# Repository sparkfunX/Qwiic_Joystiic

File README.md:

# Qwiic_Joystiic
Thumbstick Breakout for the Qwiic System
<br/><br/>
Factory Default I2C Slave Address: 0x20<br/>
<br/>
<h3 style="text-decoration: underline;">I2C Registers</h3><br/>
| Address | Contents |
| ------- | -------- |
| 0x00-0x01 | Horizontal Position (MSB First) |
| 0x02-0x03 | Vertical Position (MSB First) |
| 0x04 | Button Position |
| 0x06 | Current I2C Slave Address from EEPROM |
<br/>
<h3 style="text-decoration: underline;">I2C Commands</h3><br/>
| Address | Command |
| ------- | ------- |
| 0x05 | Set I2C Slave Address |

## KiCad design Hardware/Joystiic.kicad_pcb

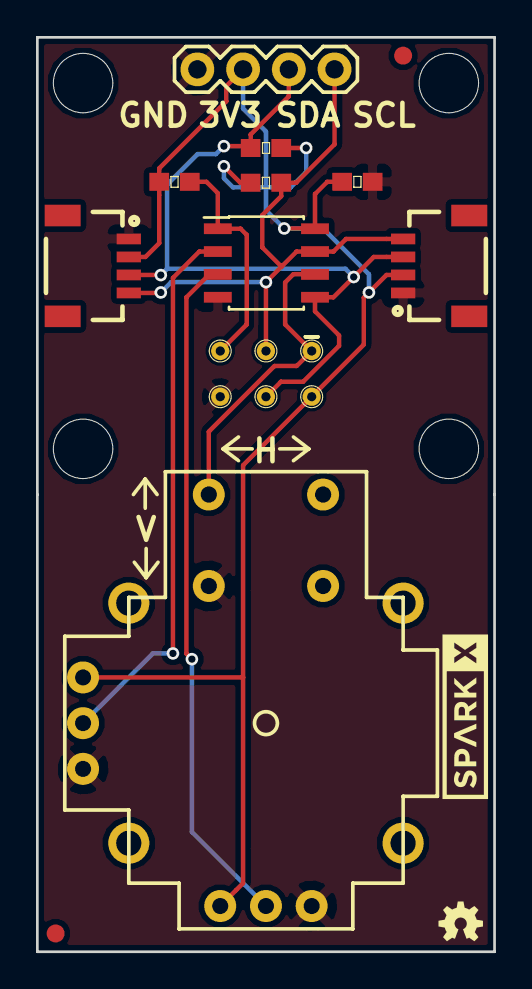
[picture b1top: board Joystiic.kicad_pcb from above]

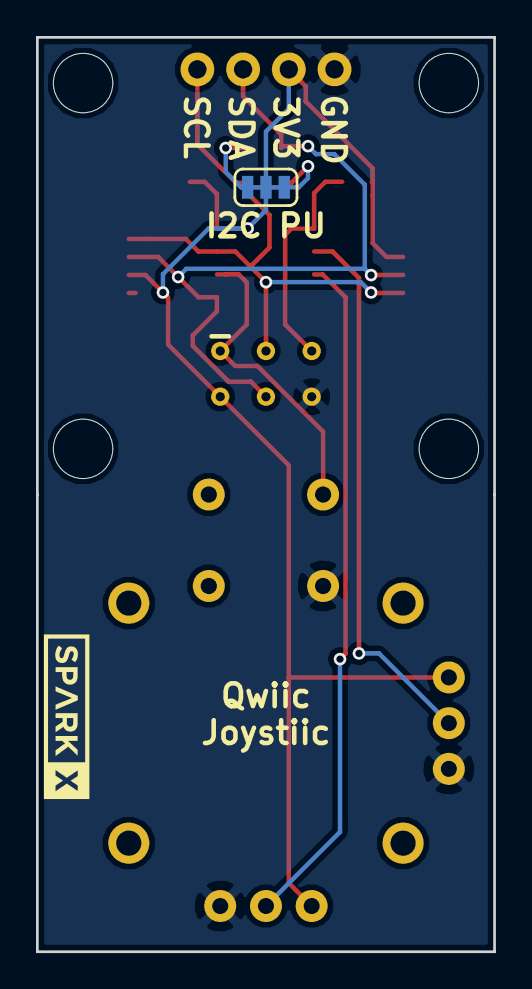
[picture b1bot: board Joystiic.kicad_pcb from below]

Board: 2 copper layers, 25.4 x 50.8 mm, 21 parts (2 on the bottom side), 10 nets.

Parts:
C1: 0.1UF-0603-25V-5%; 0603
F1, F2: Fiducial; FIDUCIAL-1X2
J1, J2: Qwiic_Connector; 1X04_1MM_RA
J3: I2C_Standard_PTH_Connector; 1X04
J4: AVR_SPI_PROG_3X2TESTPOINTS; 2X3_TEST_POINTS
JP1: JUMPER-SMT_3_2-NC_PASTE_SILK; SMT-JUMPER_3_2-NC_TRACE_SILK
LOGO1: SPARKFUN-AESTHETICS_OSHW-LOGOS; OSHW-LOGO-MINI
MK1, MK1#2, MK2, MK2#2: Mounting_Hole; STAND-OFF
R1: 10KOHM-0603-1_10W-1%; 0603
R2, R3: 4.7KOHM-0603-1_10W-1%; 0603
S1: JOYSTICK_THUMB; JOYSTICK
U1: ATTINY85-20SU; SOIC-8_3.9x4.9mm_Pitch1.27mm
U2, U3: SPARKX-LOGO4; SPARKX-MEDIUM
U4: CC_LICENSE; CREATIVE_COMMONS

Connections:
3.3V: C1.1, J1.2, J2.2, J3.2, J4.2, JP1.2, R1.1, S1.H1, S1.V1, U1.8
/HORIZONTAL: S1.H2, U1.3
/RESET: J4.5, R1.2, U1.1
/SCL: J1.4, J2.4, J3.4, J4.3, R3.2, U1.7
/SDA: J1.3, J2.3, J3.3, J4.4, R2.2, U1.5
/SELECT: J4.1, S1.B1A, U1.6
/VERTICAL: S1.V2, U1.2
GND: C1.2, J1.1, J2.1, J3.1, J4.6, S1.B2A, S1.H3, S1.V3, U1.4
unnamed: JP1.1, R3.1
unnamed: JP1.3, R2.1

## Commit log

2018-01-19 Panelized
2018-02-07 Adding Firmware and Example Code
2018-02-21 v1.1
    - Buzzard Silkscreen
    - Wide SOIC footprint
    - Power LED
2018-06-08 Added a Qwiic starter kit demo
    Uses the Joystiic, MicroOLED, and MMA8452Q accelerometer to make a snake-like game
2018-10-08 Eagle version of Joystiic
    Including the Eagle project for the Joystiic.
2018-11-19 Cleaned repo
    Cleaned up the repo, made parts sparkle parts.

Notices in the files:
parts and their libraries:
Released under the Creative Commons Attribution Share-Alike 4.0 License
https://creativecommons.org/licenses/by-sa/4.0
